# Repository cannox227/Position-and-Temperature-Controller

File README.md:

# Position-and-Temperature-Controller

## About the project 
Nowadays, more and more biomedical applications require the implementation of embedded systems, to ensure performance and reliability while keeping costs down. Currently, at the laboratories of Pro-M Facility it's developed a calibration plant for a machine used in proton therapy. 

The goal of this application is to reduce the time taken for the calibration procedure of the machinery, making the process completely autonomous and without revision, thus reducing the duration of the operation from a couple of hours to a few tens of minutes.

The project consists in the development of the measurement and control part, in support of the innovative design proposed by the company, made using: an STM32H7 microcontroller, an absolute magnetic encoder and temperature sensors.

During the entire process a bottom-up approach was used, starting from the firmware and hardware development of the individual components, and then creating interconnections between them. 

The project has been successfully completed and, at the present time, is fully integrated within the macro project of Pro-M Facility.

## Components used

Main components used for the project:
- Nucleo STM32H723ZG
- Magnetic encoder WDGA 36A
- PTC thermistor
- NTC thermistor
- Custom PCB shield
- IHM03A1 step motor driver

# The main project

The entire system is called _Matrixx_ and consists of a mechanical structure needed to support the motor and a sensors control part (this one made by us). The Python GUI and the low level drivers to drive the motor are not shown in this repo because of a nondisclosure agreement with the company. 

[Matrixx project demo video](media/Embedded%20System%20Video%20-%20Proton.mp4)

## Custom pcb shield
This PCB allows the microcontroller to handle different voltages to supply all the internal and external components (involved voltages: 3.3, 5, 24 V)<br><br>

<br>_The custom PCB used as shield_<br><br>

<br>_The control subsystem made by us_

# Build and Run
## Repo structure
    📂 Firmware
    ┣ 📂 STM F4 <- it's not the version considered in the project
    ┣ 📂 STM H7 
    📂 Hardware
    ┣ 📂 HW_Encoder_Driver_Board <- Kicad project of the first prototype (just .sch to arrange the connections) 
    ┣ 📂 HW_Temperature_Sensors_Board <- Kicad project of the PCB shield

## Build the code and run
- Open STM32 Cube IDE
- `File` > `Import` > `Existing projects into Workspace`
- Select the root directory where the project is located
- Press `Finish`

Then you can build and run using the IDE

# Report
[Full report](/Canova_Santarossa_Embedded_Systems_Project_Report.pdf)

# Credits
This project was made by:
[Tommaso Canova](https://github.com/cannox227),
[Lisa Santarossa](https://github.com/lisasnt), in collaboration with Pro-M Facility.

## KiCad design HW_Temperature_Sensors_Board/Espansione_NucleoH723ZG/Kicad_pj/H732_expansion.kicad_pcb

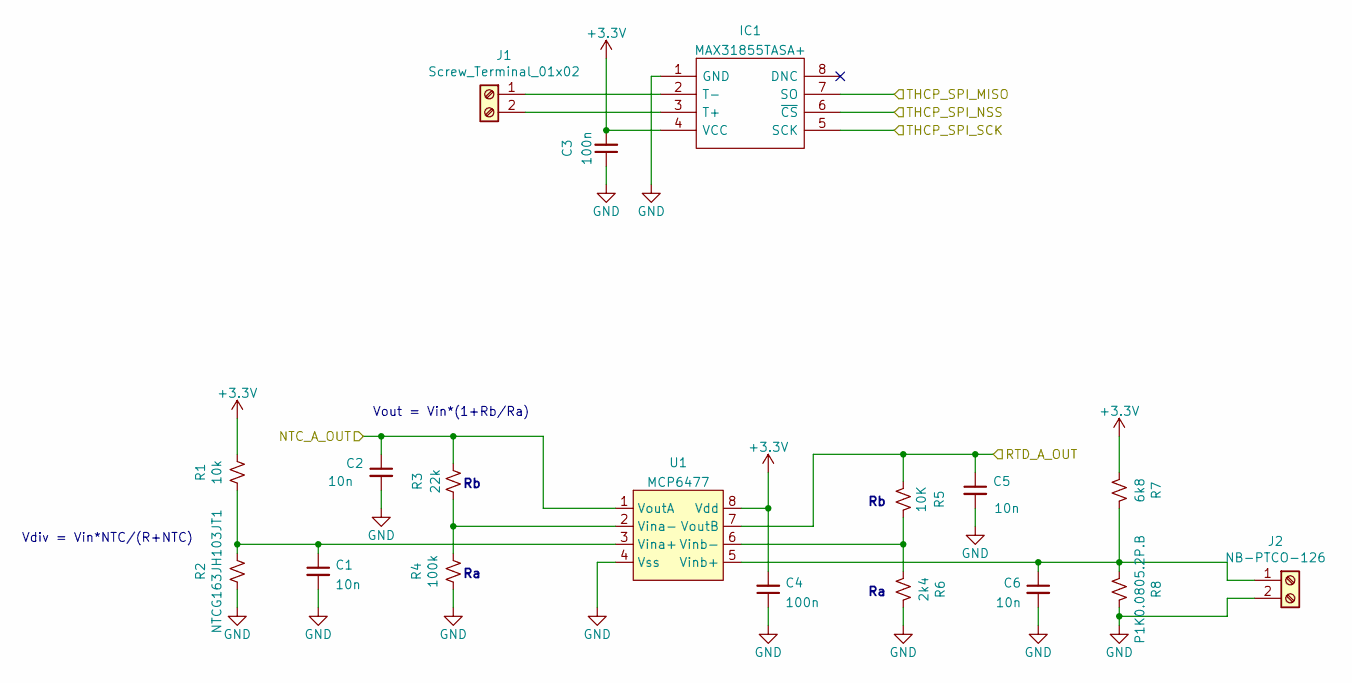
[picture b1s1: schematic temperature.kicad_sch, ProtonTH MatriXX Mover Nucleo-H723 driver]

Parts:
C1, C2, C5, C6: 10n; C_0603_1608Metric_Pad1.08x0.95mm_HandSolder
C3, C4: 100n; C_0603_1608Metric_Pad1.08x0.95mm_HandSolder
IC1: MAX31855TASA+; SOIC127P600X175-8N; Manufacturer_Part_Number MAX31855TASA+; Mouser Part Number 700-MAX31855TASA+
J1: Screw_Terminal_01x02; PinHeader_1x02_P2.54mm_Vertical
J2: NB-PTCO-126; PinHeader_1x02_P2.54mm_Vertical
R1: 10k; R_0603_1608Metric_Pad0.98x0.95mm_HandSolder
R2: NTCG163JH103JT1; R_0603_1608Metric_Pad0.98x0.95mm_HandSolder
R3: 22k; R_0603_1608Metric_Pad0.98x0.95mm_HandSolder
R4: 100k; R_0603_1608Metric_Pad0.98x0.95mm_HandSolder
R5: 10K; R_0603_1608Metric_Pad0.98x0.95mm_HandSolder
R6: 2k4; R_0603_1608Metric_Pad0.98x0.95mm_HandSolder
R7: 6k8; R_0603_1608Metric_Pad0.98x0.95mm_HandSolder
R8: P1K0.0805.2P.B; R_0805_2012Metric_Pad1.20x1.40mm_HandSolder
U1: MCP6477; SOIC-8_3.9x4.9mm_P1.27mm

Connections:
+3V3: C3.2, C4.2, IC1.4 (VCC), R1.2, R7.2, U1.8 (Vdd); also elsewhere on the board
/connectors/NTC_A_OUT: C2.1, R3.2, U1.1 (VoutA); also elsewhere on the board
/connectors/RTD_A_OUT: C5.1, R5.2, U1.7 (VoutB); also elsewhere on the board
/connectors/THCP_SPI_MISO: IC1.7 (SO); also elsewhere on the board
/connectors/THCP_SPI_NSS: IC1.6 (~CS); also elsewhere on the board
/connectors/THCP_SPI_SCK: IC1.5 (SCK); also elsewhere on the board
GND: C1.2, C2.2, C3.1, C4.1, C5.2, C6.2, IC1.1 (GND), J2.2, R2.1, R4.1, R6.1, R8.1, U1.4 (Vss); also elsewhere on the board
unnamed: C1.1, R1.1, R2.2, U1.3 (Vina+)
unnamed: C6.1, J2.1, R7.1, R8.2, U1.5 (Vinb+)
unnamed: IC1.2 (T-), J1.1
unnamed: IC1.3 (T+), J1.2
unnamed: R3.1, R4.2, U1.2 (Vina-)
unnamed: R5.1, R6.2, U1.6 (Vinb-)

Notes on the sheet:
Vdiv = Vin*NTC/(R+NTC)
Vout = Vin*(1+Rb/Ra)

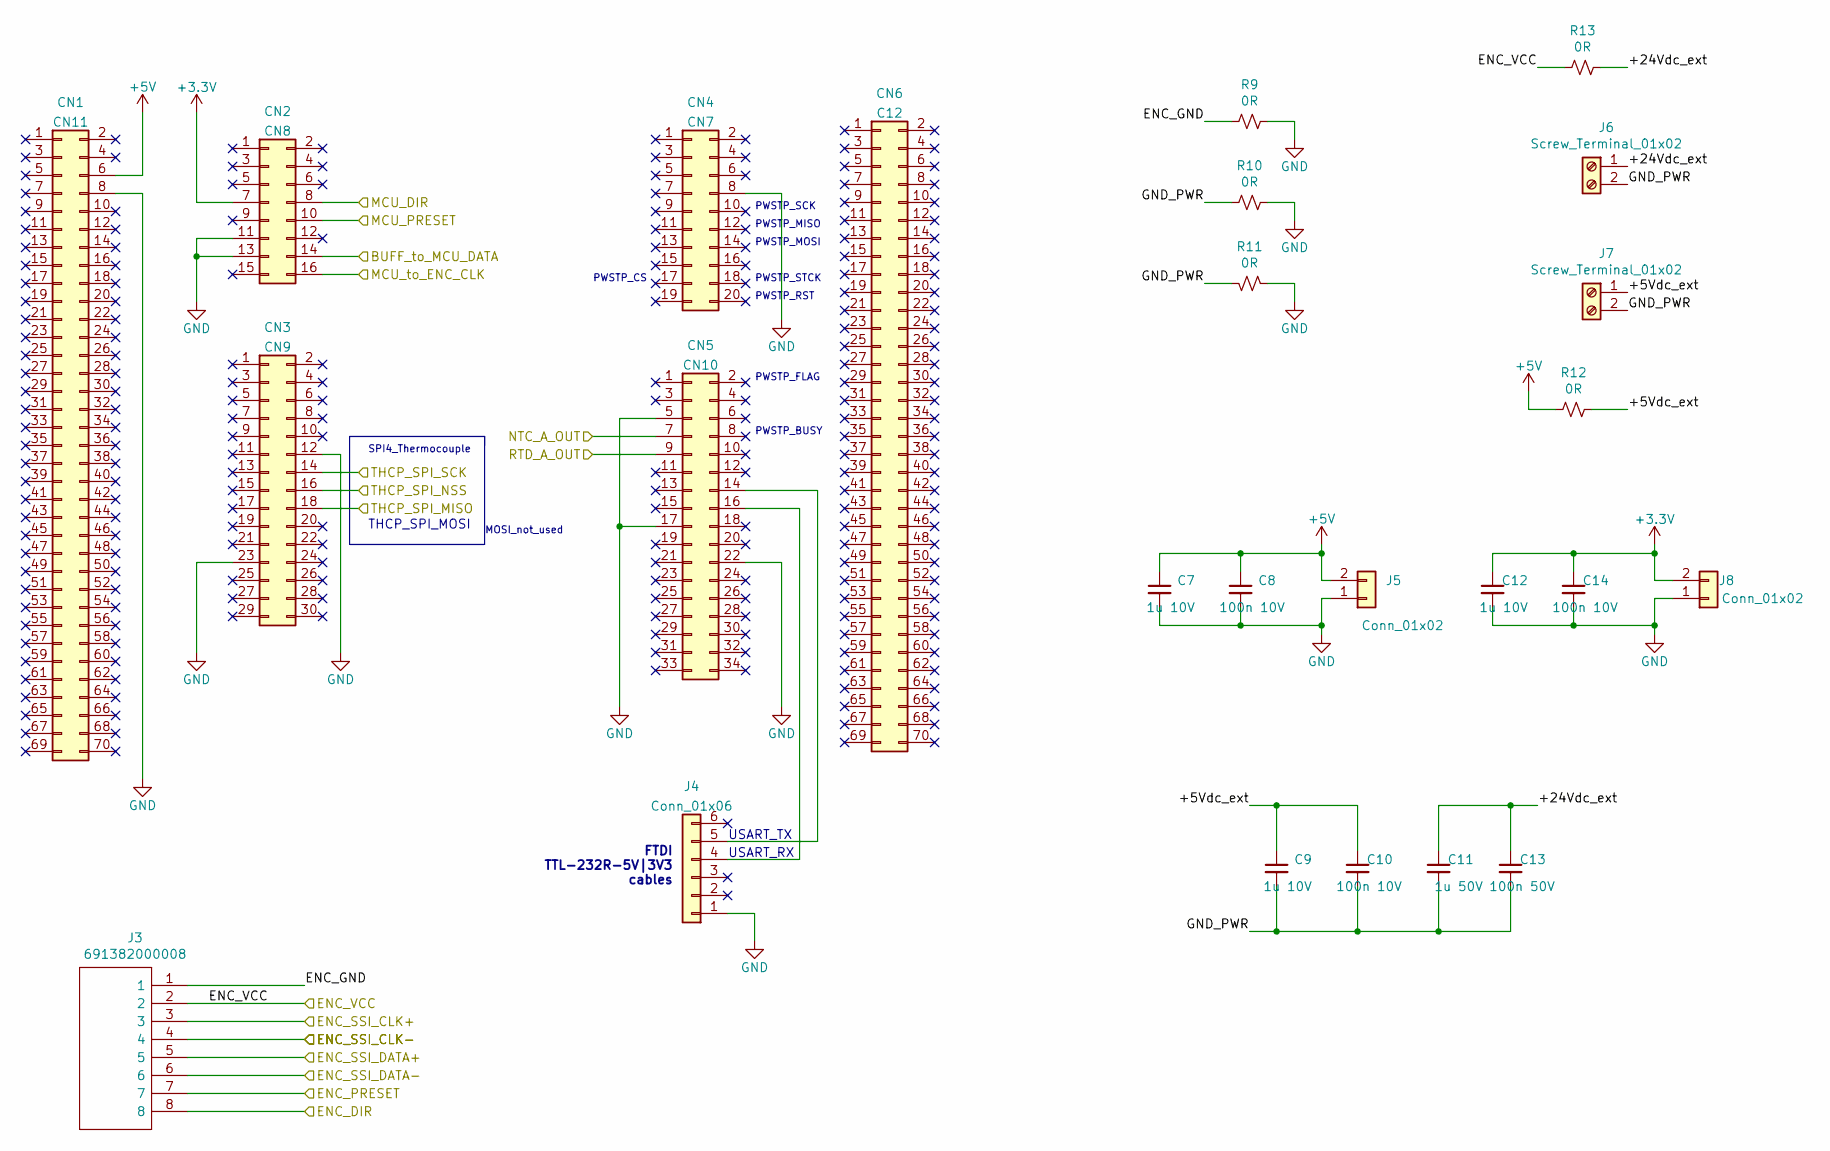
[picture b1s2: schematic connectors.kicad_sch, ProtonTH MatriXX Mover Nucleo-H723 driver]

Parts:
C7, C9, C12: 1u 10V; C_0805_2012Metric_Pad1.18x1.45mm_HandSolder
C8, C10, C14: 100n 10V; C_0603_1608Metric_Pad1.08x0.95mm_HandSolder
C11: 1u 50V; C_0805_2012Metric_Pad1.18x1.45mm_HandSolder
C13: 100n 50V; C_0603_1608Metric_Pad1.08x0.95mm_HandSolder
CN1: CN11; PinHeader_2x35_P2.54mm_Vertical
CN2: CN8; PinHeader_2x08_P2.54mm_Vertical
CN3: CN9; PinHeader_2x15_P2.54mm_Vertical
CN4: CN7; PinHeader_2x10_P2.54mm_Vertical
CN5: CN10; PinHeader_2x17_P2.54mm_Vertical
CN6: C12; PinHeader_2x35_P2.54mm_Vertical
J3: 691382000008; SHDR8W80P0X250_1X8_2200X810X1010P; Manufacturer_Part_Number 691382000008; Mouser Part Number 710-691382000008
J4: Conn_01x06; PinHeader_1x06_P2.54mm_Vertical
J5, J8: Conn_01x02; PinHeader_1x02_P2.54mm_Vertical
J6, J7: Screw_Terminal_01x02; PinHeader_1x02_P2.54mm_Vertical
R9, R10, R11, R12, R13: 0R; R_0603_1608Metric_Pad0.98x0.95mm_HandSolder

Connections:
+3V3: C12.1, C14.1, CN2.7, J8.2; also elsewhere on the board
+5V: C7.1, C8.1, CN1.6, J5.2, R12.1; also elsewhere on the board
/connectors/+5Vdc_ext: C9.1, C10.1, J7.1, R12.2
/connectors/+24Vdc_ext: C11.1, C13.1, J6.1, R13.2
/connectors/BUFF_to_MCU_DATA: CN2.14; also elsewhere on the board
/connectors/ENC_DIR: J3.8; also elsewhere on the board
/connectors/ENC_GND: J3.1, R9.1
/connectors/ENC_PRESET: J3.7; also elsewhere on the board
/connectors/ENC_SSI_CLK+: J3.3; also elsewhere on the board
/connectors/ENC_SSI_CLK-: J3.4; also elsewhere on the board
/connectors/ENC_SSI_DATA+: J3.5; also elsewhere on the board
/connectors/ENC_SSI_DATA-: J3.6; also elsewhere on the board
/connectors/ENC_VCC: J3.2, R13.1; also elsewhere on the board
/connectors/GND_PWR: C9.2, C10.2, C11.2, C13.2, J6.2, J7.2, R10.1, R11.2
/connectors/MCU_DIR: CN2.8; also elsewhere on the board
/connectors/MCU_PRESET: CN2.10; also elsewhere on the board
/connectors/MCU_to_ENC_CLK: CN2.16; also elsewhere on the board
/connectors/NTC_A_OUT: CN5.7; also elsewhere on the board
/connectors/RTD_A_OUT: CN5.9; also elsewhere on the board
/connectors/THCP_SPI_MISO: CN3.18; also elsewhere on the board
/connectors/THCP_SPI_NSS: CN3.16; also elsewhere on the board
/connectors/THCP_SPI_SCK: CN3.14; also elsewhere on the board
GND: C7.2, C8.2, C12.2, C14.2, CN1.8, CN2.11, CN2.13, CN3.12, CN3.23, CN4.8, CN5.5, CN5.17, CN5.22, J4.1, J5.1, J8.1, R9.2, R10.2, R11.1; also elsewhere on the board
unnamed: CN5.14, J4.5
unnamed: CN5.16, J4.4

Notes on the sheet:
PWSTP_BUSY
PWSTP_FLAG
MOSI_not_used
FTDI TTL-232R-5V|3V3 cables
PWSTP_CS
PWSTP_MOSI
PWSTP_MISO
USART_TX
THCP_SPI_MOSI
PWSTP_STCK
PWSTP_RST
PWSTP_SCK
USART_RX
SPI4_Thermocouple

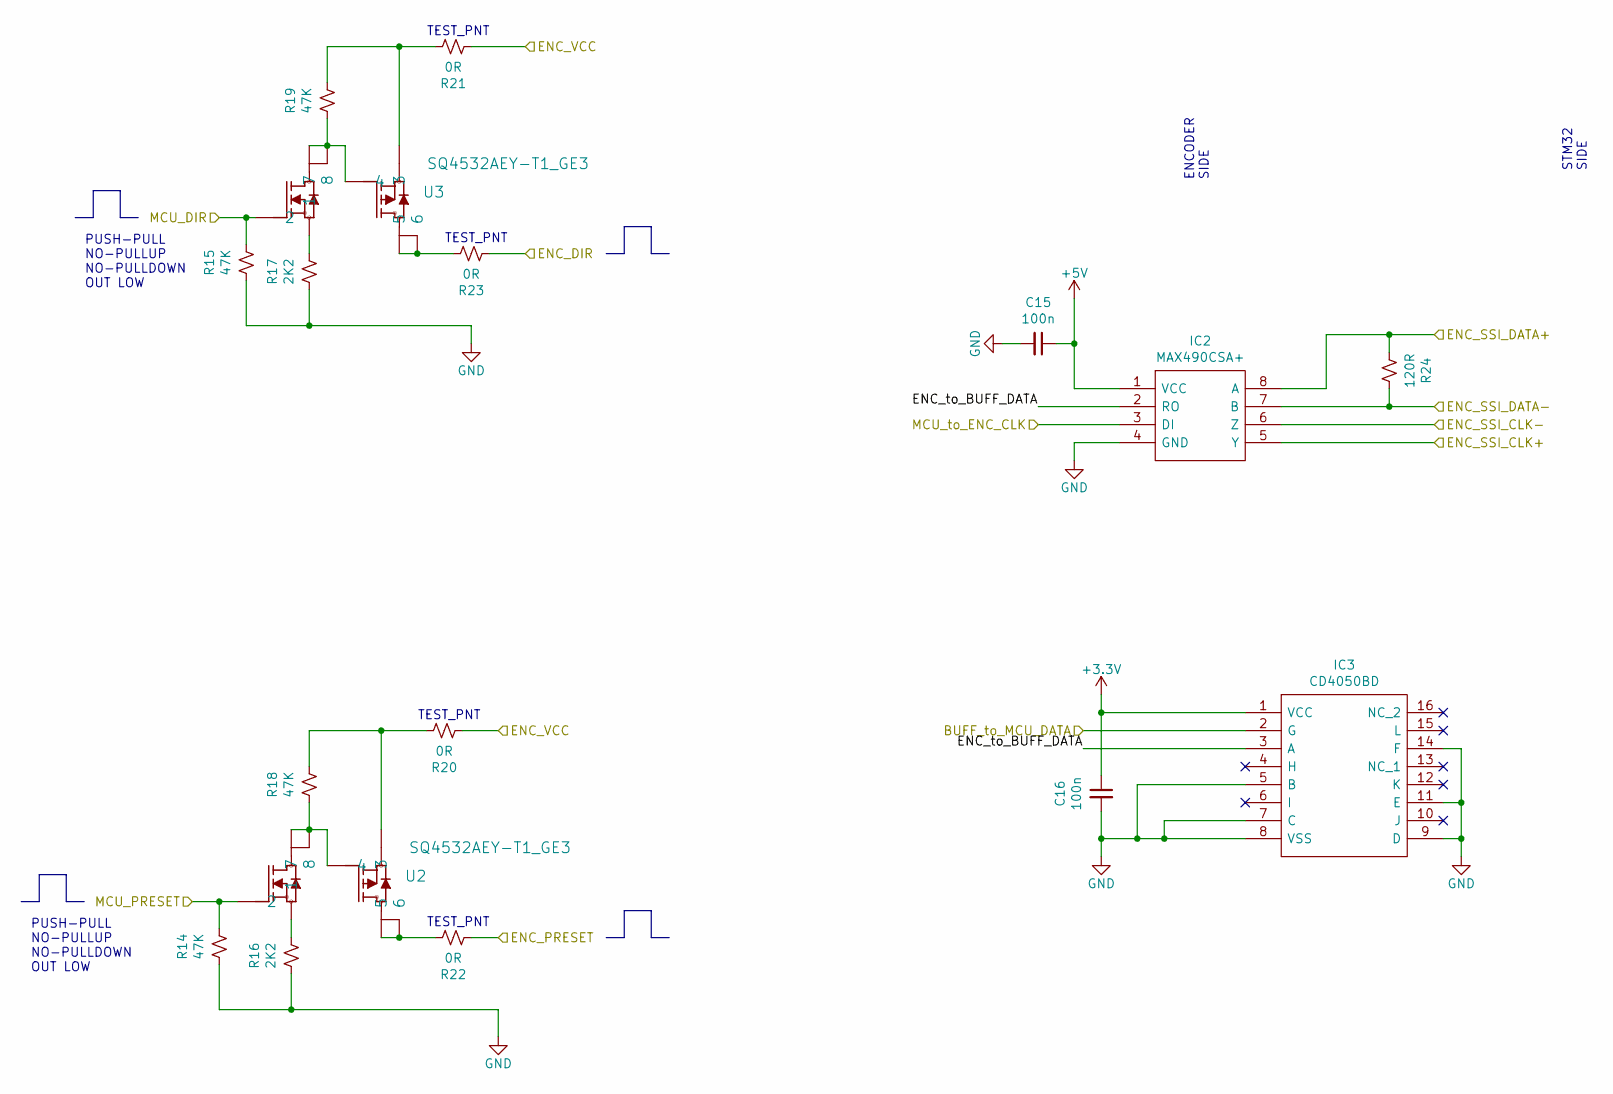
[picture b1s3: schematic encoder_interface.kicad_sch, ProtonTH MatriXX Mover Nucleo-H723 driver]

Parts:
C15, C16: 100n; C_0603_1608Metric_Pad1.08x0.95mm_HandSolder
IC2: MAX490CSA+; SOIC127P600X175-8N; Manufacturer_Part_Number MAX490CSA+; Mouser Part Number 700-MAX490CSA
IC3: CD4050BD; SOIC127P600X175-16N; Manufacturer_Part_Number CD4050BD; Mouser Part Number 595-CD4050BD
R14, R15, R18, R19: 47K; R_0603_1608Metric_Pad0.98x0.95mm_HandSolder
R16, R17: 2K2; R_0603_1608Metric_Pad0.98x0.95mm_HandSolder
R20, R21, R22, R23: 0R; R_0603_1608Metric_Pad0.98x0.95mm_HandSolder
R24: 120R; R_0603_1608Metric_Pad0.98x0.95mm_HandSolder
U2, U3: SQ4532AEY-T1_GE3

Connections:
+3V3: C16.1, IC3.1 (VCC); also elsewhere on the board
+5V: C15.1, IC2.1 (VCC); also elsewhere on the board
/connectors/BUFF_to_MCU_DATA: IC3.2 (G); also elsewhere on the board
/connectors/ENC_DIR: R23.1; also elsewhere on the board
/connectors/ENC_PRESET: R22.1; also elsewhere on the board
/connectors/ENC_SSI_CLK+: IC2.5 (Y); also elsewhere on the board
/connectors/ENC_SSI_CLK-: IC2.6 (Z); also elsewhere on the board
/connectors/ENC_SSI_DATA+: IC2.8 (A), R24.1; also elsewhere on the board
/connectors/ENC_SSI_DATA-: IC2.7 (B), R24.2; also elsewhere on the board
/connectors/ENC_VCC: R20.1, R21.1; also elsewhere on the board
/connectors/MCU_DIR: R15.2, U3.2; also elsewhere on the board
/connectors/MCU_PRESET: R14.2, U2.2; also elsewhere on the board
/connectors/MCU_to_ENC_CLK: IC2.3 (DI); also elsewhere on the board
/encoder_interface/ENC_to_BUFF_DATA: IC2.2 (RO), IC3.3 (A)
GND: C15.2, C16.2, IC2.4 (GND), IC3.5 (B), IC3.7 (C), IC3.8 (VSS), IC3.9 (D), IC3.11 (E), IC3.14 (F), R14.1, R15.1, R16.1, R17.1; also elsewhere on the board
unnamed: R16.2, U2.1
unnamed: R17.2, U3.1
unnamed: R18.1, U2.4, U2.7, U2.8
unnamed: R18.2, R20.2, U2.3
unnamed: R19.1, U3.4, U3.7, U3.8
unnamed: R19.2, R21.2, U3.3
unnamed: R22.2, U2.5, U2.6
unnamed: R23.2, U3.5, U3.6

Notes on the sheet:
TEST_PNT
STM32 SIDE
PUSH-PULL NO-PULLUP NO-PULLDOWN OUT LOW
ENCODER SIDE

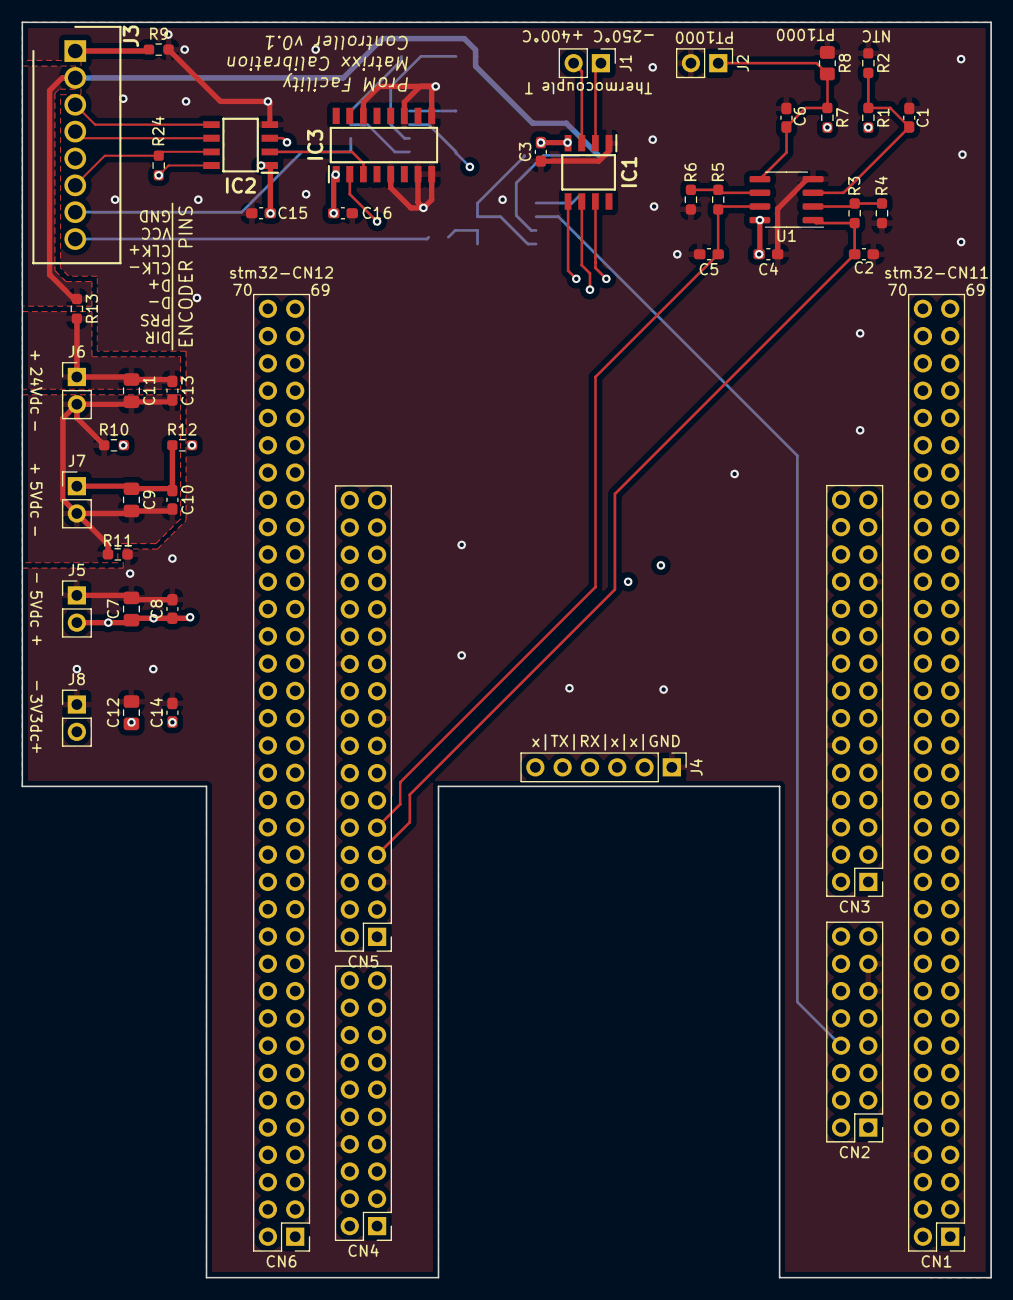
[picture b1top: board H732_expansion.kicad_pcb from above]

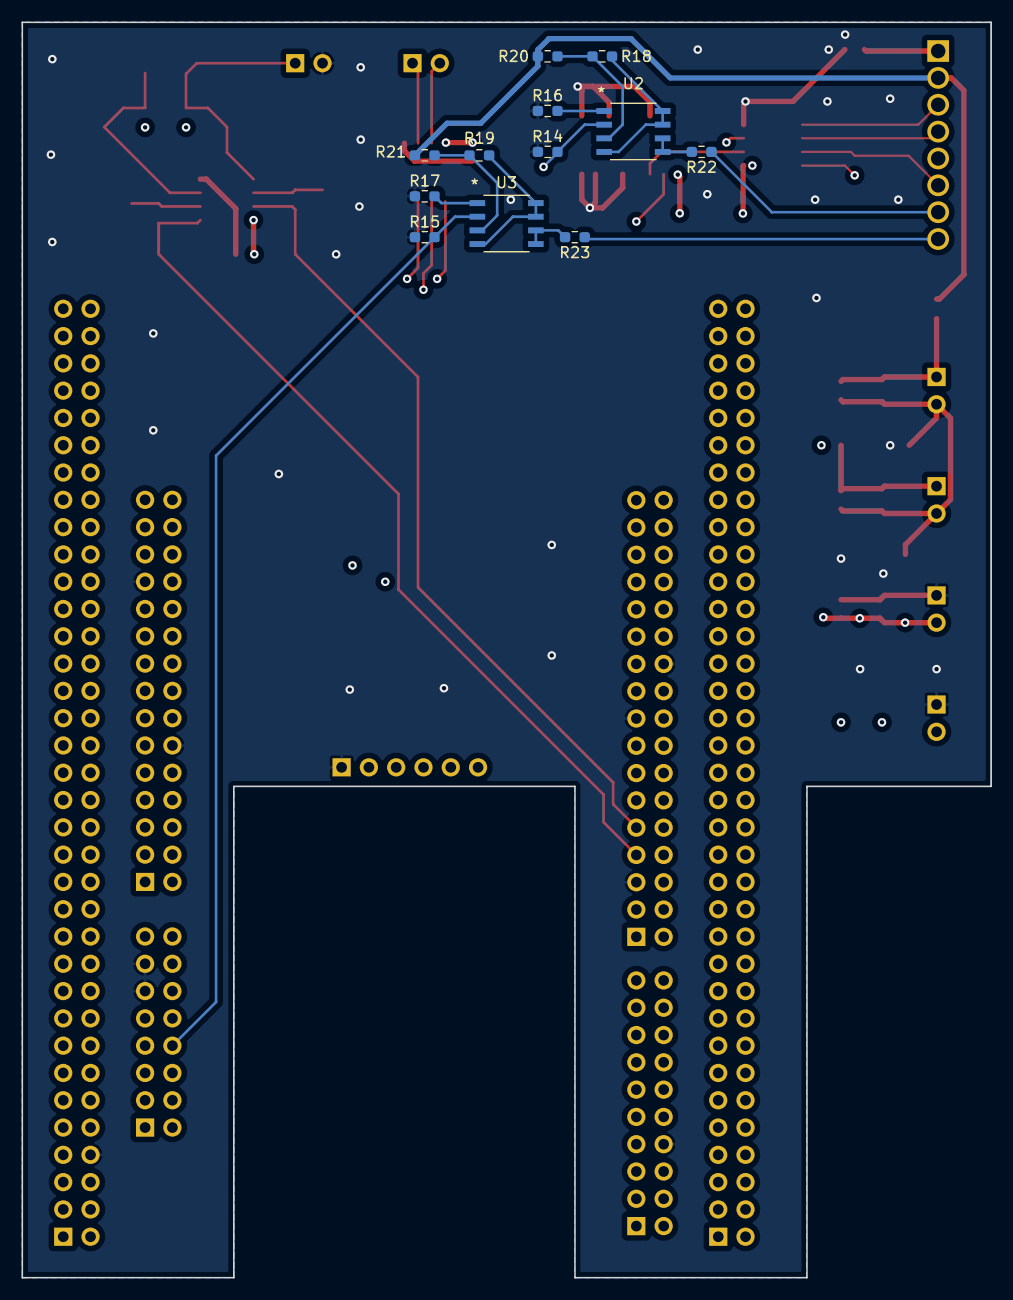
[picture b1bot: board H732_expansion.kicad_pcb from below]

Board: 4 copper layers, 90.2 x 116.8 mm, 60 parts (12 on the bottom side), 40 nets.

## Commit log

2022-03-15 Add kicad folder and rename cubemx project
2022-03-15 Add Datasheets Folder
2022-03-22 Folder rename
2022-03-22 fw: added to ioc ntc e pt1000
2022-03-22 other: added basic readme
2022-03-22 fw: added ntc basic structure
2022-03-22 fw: added ntc demo
2022-03-23 other: change .gitignore
2022-03-23 fw: pt1000 code v.0
2022-03-23 fw: refactor pt1000->ptc
2022-03-23 fw: ntc and ptc update v0
2022-03-23 fw: ptc works fine
2022-03-25 fw: fixed includes
2022-03-25 fw: fixed multiple defs
2022-03-25 fw: fix lib dependencies
2022-03-25 fw: add ide_settings.xml
2022-03-25 fw: ntc and ptc work fine
2022-03-29 fw: main update
2022-03-30 fw: ptc calibration added
2022-03-30 fw: optimized calibration for ntc and ptc
2022-03-30 doc+fw: update excel and change of C1, C2
2022-03-30 fw: add encoder
2022-04-05 fw: timer11 to be fixed
2022-04-12 fw: add H7 encoder reading
2022-04-12 fw: add ntc and ptc, calibration needed
2022-04-13 fw: changed output format for encoder and temperatures
2022-04-26 fix: longer preset time and further calibration
2022-04-27 hw: connectors update
2022-05-03 fw: add angle conversion comments
2022-07-02 clean up the repo and add readme
2022-07-02 add project report
2023-04-28 chore: add dataset tree view

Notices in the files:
parts and their libraries:
Copyright 2021 Accelerated Designs. All rights reserved.
